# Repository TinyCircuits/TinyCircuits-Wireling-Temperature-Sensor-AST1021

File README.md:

# TinyCircuits Wireling Temperature Sensor
# AST1021 Rev2

The design files are located under design_files/ for the TinyCircuits AST1021 Rev 2 PCB. This is a Wireling board which features the PCT2075 Temperature Senor with 11-bit output. You've probably already guessed correctly that this sensor helps you measure the temperature in a given environment.

Format is in Cadsoft Eagle format - Eagle version 6.2 was used for the original design.

For more infomation on this, check out the product page at TinyCircuits.com

# License:

Design by TinyCircuits.
All design files are released under the Creative Commons Attribution Share-Alike 3.0 License, see the following link for details: http://creativecommons.org/licenses/by-sa/3.0

All text above must be included in any redistribution or derived design

This project uses designs and concepts developed as part of the Arduino project and the LilyPad project.  The TinyCircuits design files themselves (schematics, PCB and libraries) are not directly derived from these works' design files and have been created new, however the concepts and basic architecture behind the TinyDuino and TinyLily products are derived and we thank the hard work of the organizations below for their contributions to open-source hardware:
  
Original Arduino Uno Design by Team Arduino

LilyPad Arduino Design by Leah Buechley and Sparkfun Electronics

Please support the open-source hardware community

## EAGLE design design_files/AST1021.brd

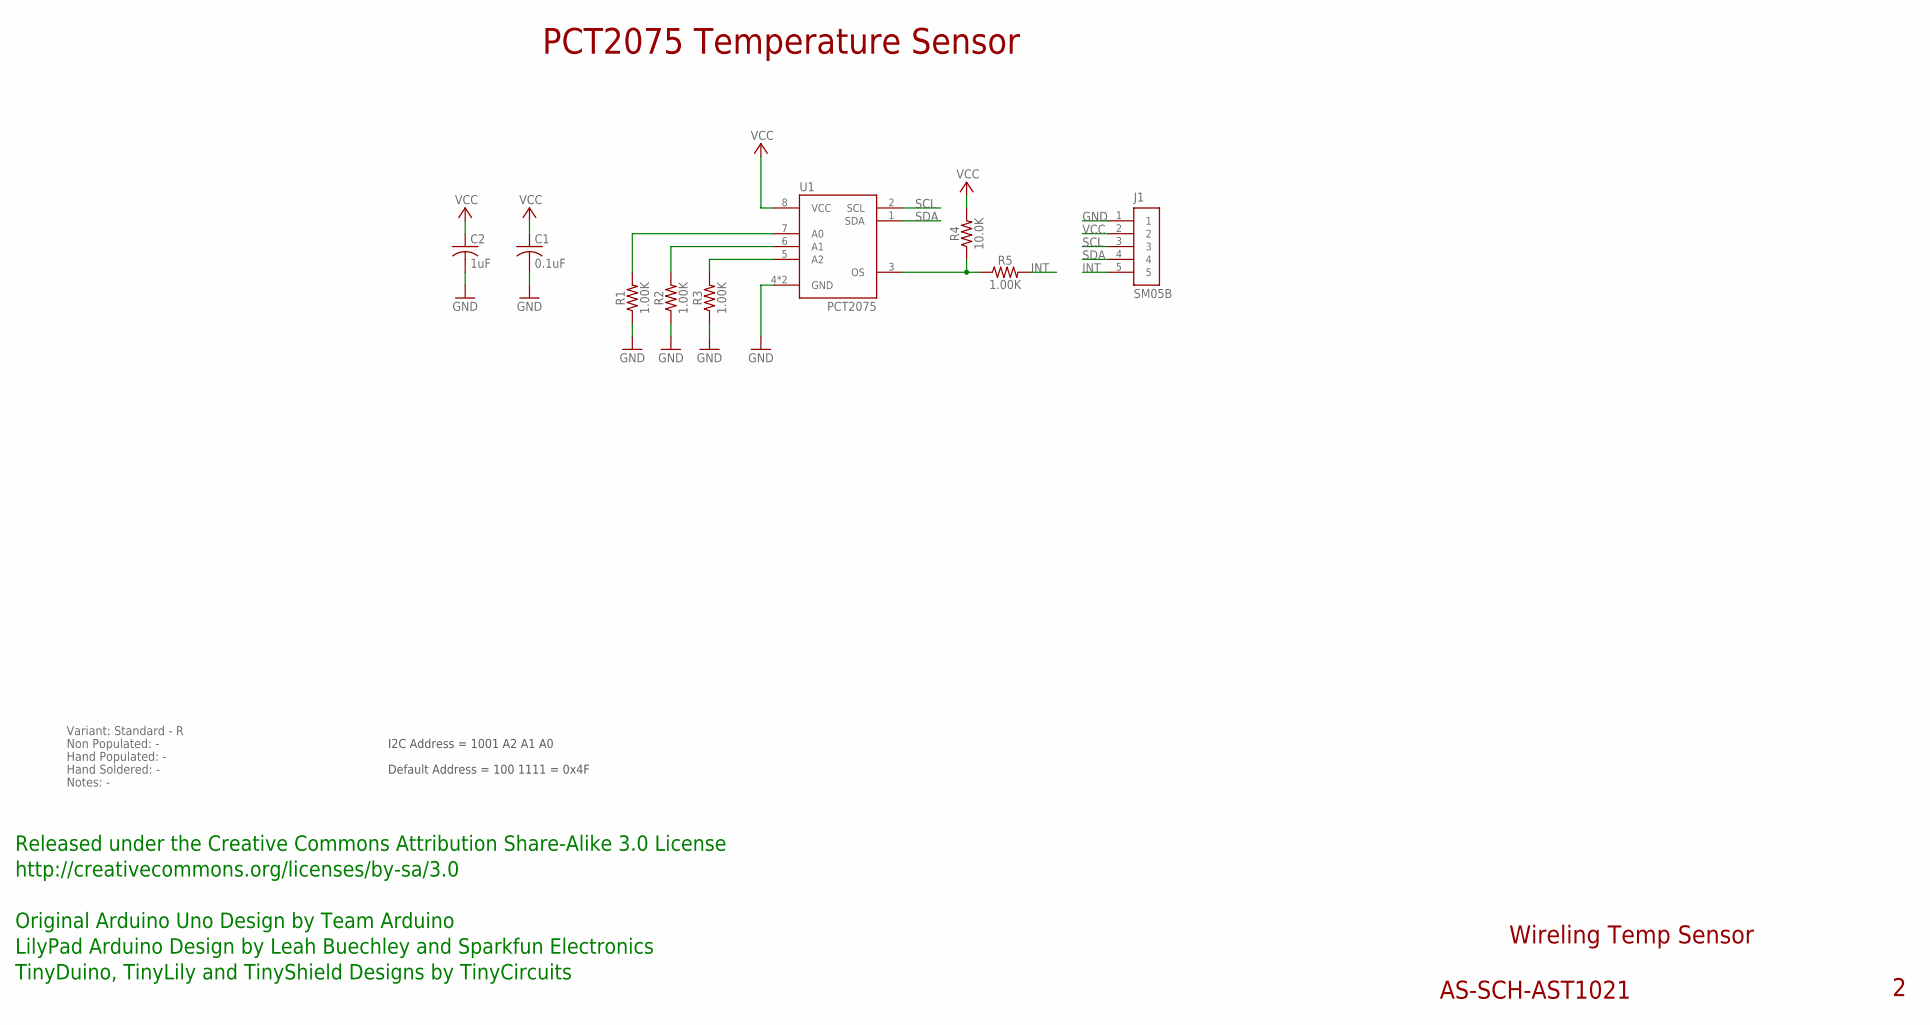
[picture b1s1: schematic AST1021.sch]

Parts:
C1: 0.1uF; C0402
C2: 1uF; C0603; PARTNO AS-ITM-00410
J1: SM05B; JST_SH_5X1_EDGE
R1, R2, R3, R5: 1.00K; 0402; PARTNO AS-ITM-00003
R4: 10.0K; 0402
U1: PCT2075; HWSON-8

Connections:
GND: C1.2, C2.2, J1.1, R1.1, R2.1, R3.1, U1.4 (GND), U1.GND
GPIO1: R4.1, R5.1, U1.3 (OS)
INT: J1.5, R5.2
unnamed: R1.2, U1.7 (A0)
unnamed: R2.2, U1.6 (A1)
unnamed: R3.2, U1.5 (A2)
SCL: J1.3, U1.2 (SCL)
SDA: J1.4, U1.1 (SDA)
VCC: C1.1, C2.1, J1.2, R4.2, U1.8 (VCC)

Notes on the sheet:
Wireling Temp Sensor
AS-SCH-AST1021
PCT2075 Temperature Sensor
Released under the Creative Commons Attribution Share-Alike 3.0 License
http://creativecommons.org/licenses/by-sa/3.0
Original Arduino Uno Design by Team Arduino
TinyDuino, TinyLily and TinyShield Designs by TinyCircuits
LilyPad Arduino Design by Leah Buechley and Sparkfun Electronics
I2C Address = 1001 A2 A1 A0
Default Address = 100 1111 = 0x4F
Variant: Standard - R
Non Populated: -
Hand Populated: -
Hand Soldered: -
Notes: -

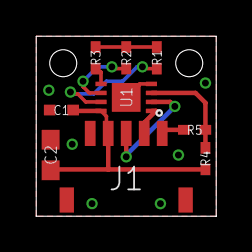
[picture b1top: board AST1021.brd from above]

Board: 2 copper layers, 10.0 x 10.0 mm, 10 parts (0 on the bottom side), 9 nets.

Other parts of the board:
U$1: DOCFIELD-TINYCIRCUITS-PCB

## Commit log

2019-08-08 added necessary folders
2019-09-17 schem
2019-10-29 name change
2019-12-26 added image
2019-12-30 updated documentation
2020-01-11 temp
2020-01-11 new iamges
2020-01-11 images
2020-02-04 mass image update
2020-06-04 what happened here hmm
2020-08-14 Add CAD data
2022-01-25 add simplified example
